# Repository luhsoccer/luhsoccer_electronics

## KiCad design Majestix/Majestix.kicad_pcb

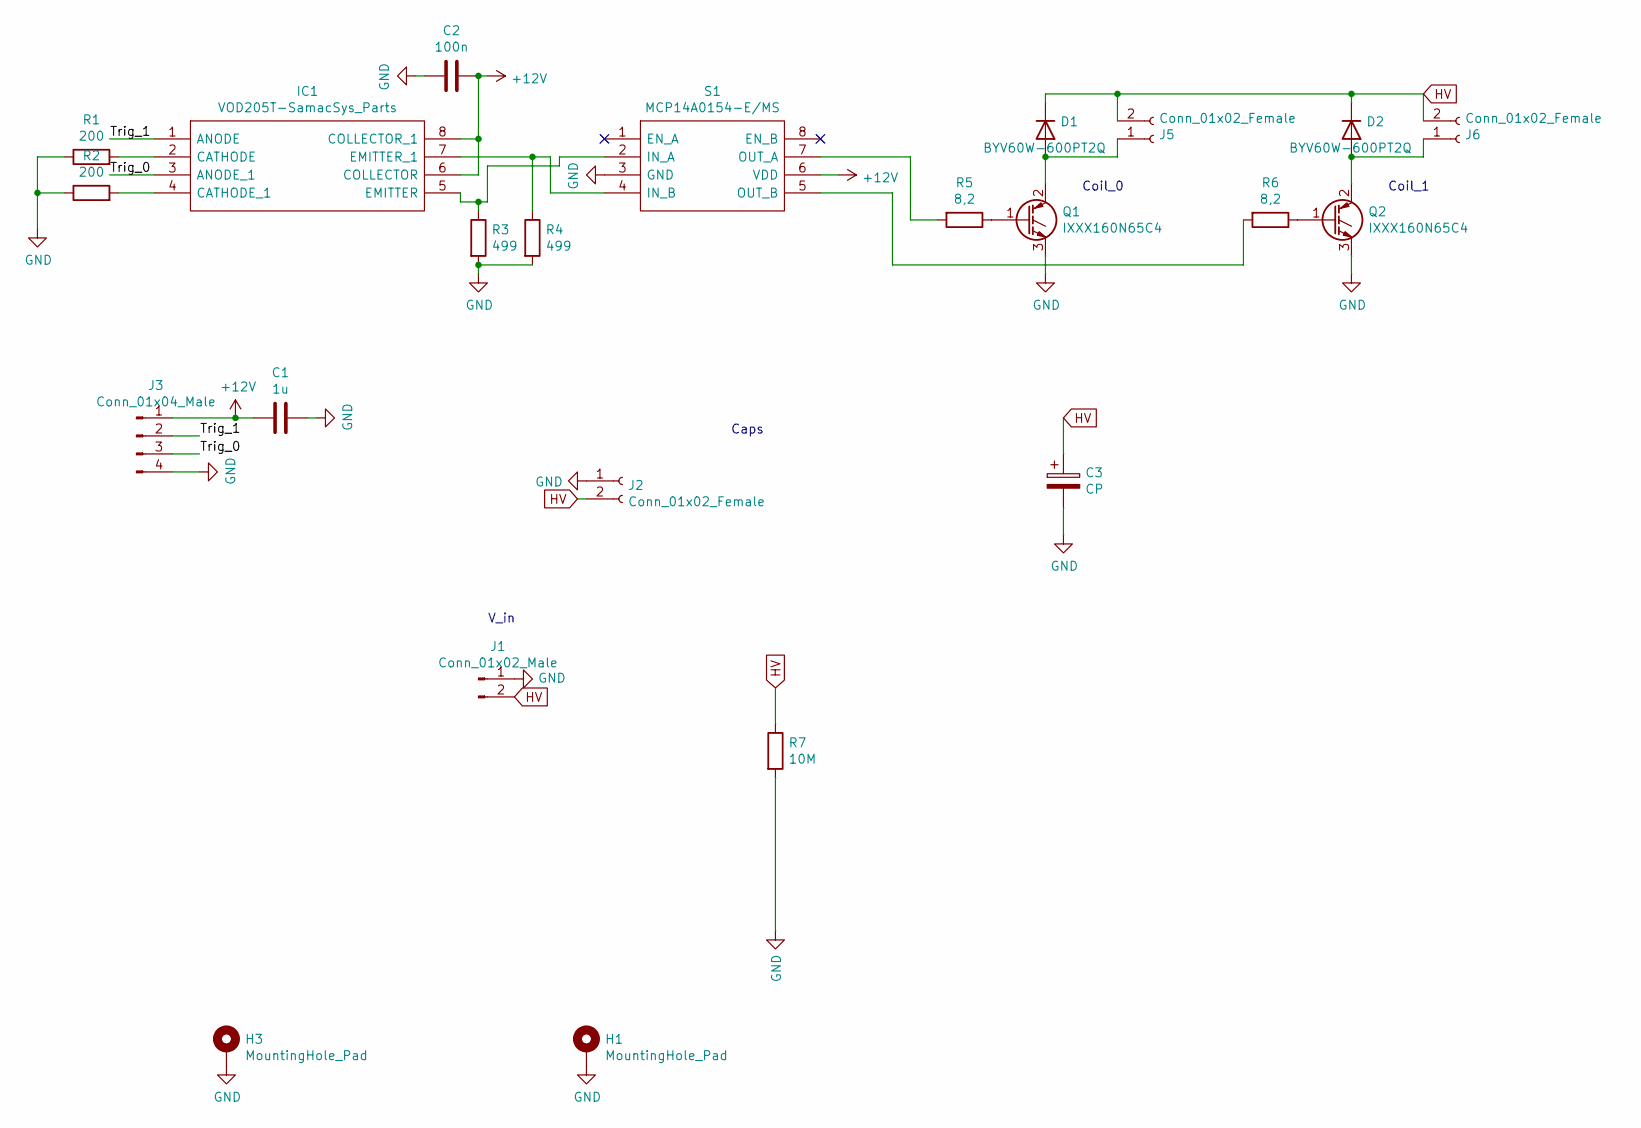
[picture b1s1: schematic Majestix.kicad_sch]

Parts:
C1: 1u; C_0805_2012Metric_Pad1.15x1.40mm_HandSolder
C2: 100n; C_0805_2012Metric_Pad1.15x1.40mm_HandSolder
C3: CP; CP_Radial_D30.0mm_P10.00mm_SnapIn
D1, D2: BYV60W-600PT2Q; TO-247-2_Vertical
H1, H3: MountingHole_Pad; MountingHole_3.2mm_M3_Pad_Via
IC1: VOD205T-SamacSys_Parts; SOIC-8_3.9x4.9mm_P1.27mm; Mouser Part Number 78-VOD205T
J1: Conn_01x02_Male; Molex_Micro-Fit_3.0_43650-0215_1x02_P3.00mm_Vertical
J2: Conn_01x02_Female; AMASS_XT30U-F_1x02_P5.0mm_Vertical_modified
J3: Conn_01x04_Male; JST_PH_B4B-PH-K_1x04_P2.00mm_Vertical
J5, J6: Conn_01x02_Female; AMASS_XT60-F_1x02_P7.20mm_Vertical_modified
Q1, Q2: IXXX160N65C4; TO-247-3_Vertical
R1, R2: 200; R_0805_2012Metric_Pad1.15x1.40mm_HandSolder
R3, R4: 499; R_0805_2012Metric_Pad1.15x1.40mm_HandSolder
R5, R6: 8,2; R_0805_2012Metric_Pad1.15x1.40mm_HandSolder
R7: 10M; R_2010_5025Metric_Pad1.52x2.65mm_HandSolder
S1: MCP14A0154-E/MS; MSOP-8_3x3mm_P0.65mm; Mouser Part Number 579-MCP14A0154-E/MS

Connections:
+12V: C1.2, C2.1, IC1.6 (COLLECTOR), IC1.8 (COLLECTOR_1), J3.1, S1.6 (VDD)
/Trig_0: IC1.3 (ANODE_1), J3.3
/Trig_1: IC1.1 (ANODE), J3.2
GND: C1.1, C2.2, C3.2, H1.1, H3.1, J1.1, J2.1, J3.4, Q1.3 (E), Q2.3 (E), R1.1, R2.1, R3.2, R4.2, R7.2, S1.3 (GND)
HV: C3.1, D1.1 (K), D2.1 (K), J1.2, J2.2, J5.2, J6.2, R7.1
unnamed: D1.2 (A), J5.1, Q1.2 (C)
unnamed: D2.2 (A), J6.1, Q2.2 (C)
unnamed: IC1.2 (CATHODE), R1.2
unnamed: IC1.4 (CATHODE_1), R2.2
unnamed: IC1.5 (EMITTER), R3.1, S1.2 (IN_A)
unnamed: IC1.7 (EMITTER_1), R4.1, S1.4 (IN_B)
unnamed: Q1.1 (G), R5.1
unnamed: Q2.1 (G), R6.1
unnamed: R5.2, S1.7 (OUT_A)
unnamed: R6.2, S1.5 (OUT_B)

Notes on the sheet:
Coil_0
V_in
Coil_1
Caps

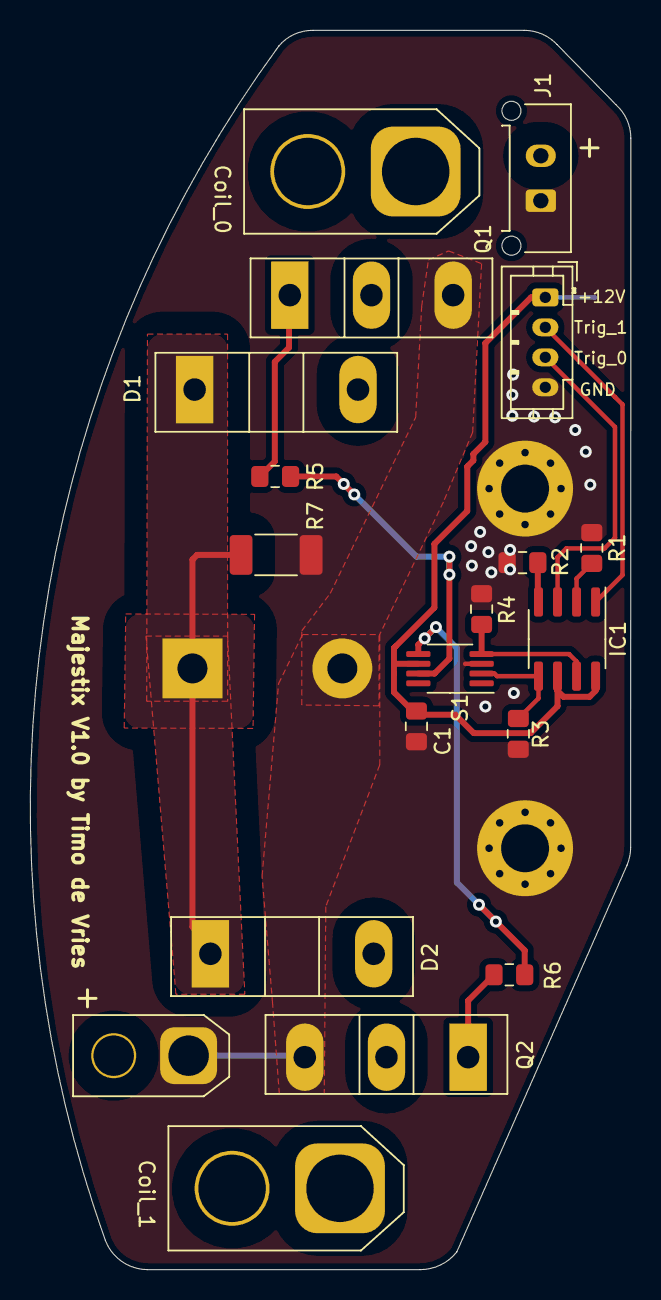
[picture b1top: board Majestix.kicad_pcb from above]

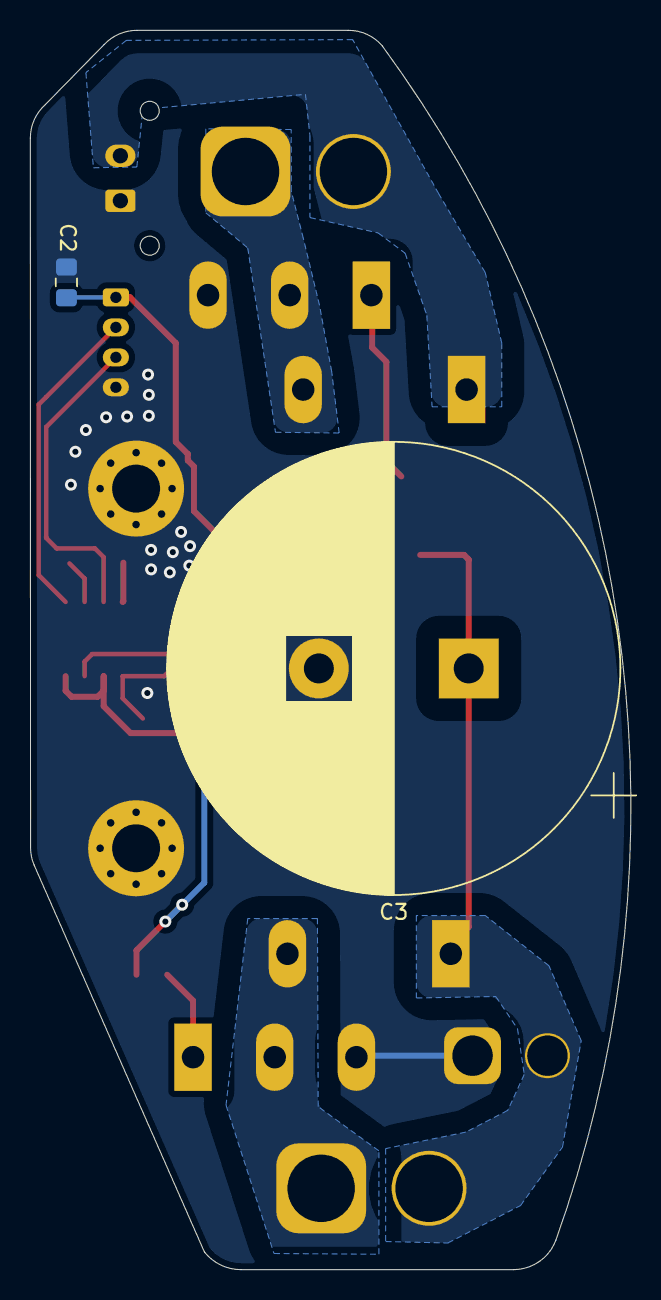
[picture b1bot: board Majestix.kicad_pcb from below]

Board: 2 copper layers, 40.1 x 82.7 mm, 23 parts (2 on the bottom side), 15 nets.

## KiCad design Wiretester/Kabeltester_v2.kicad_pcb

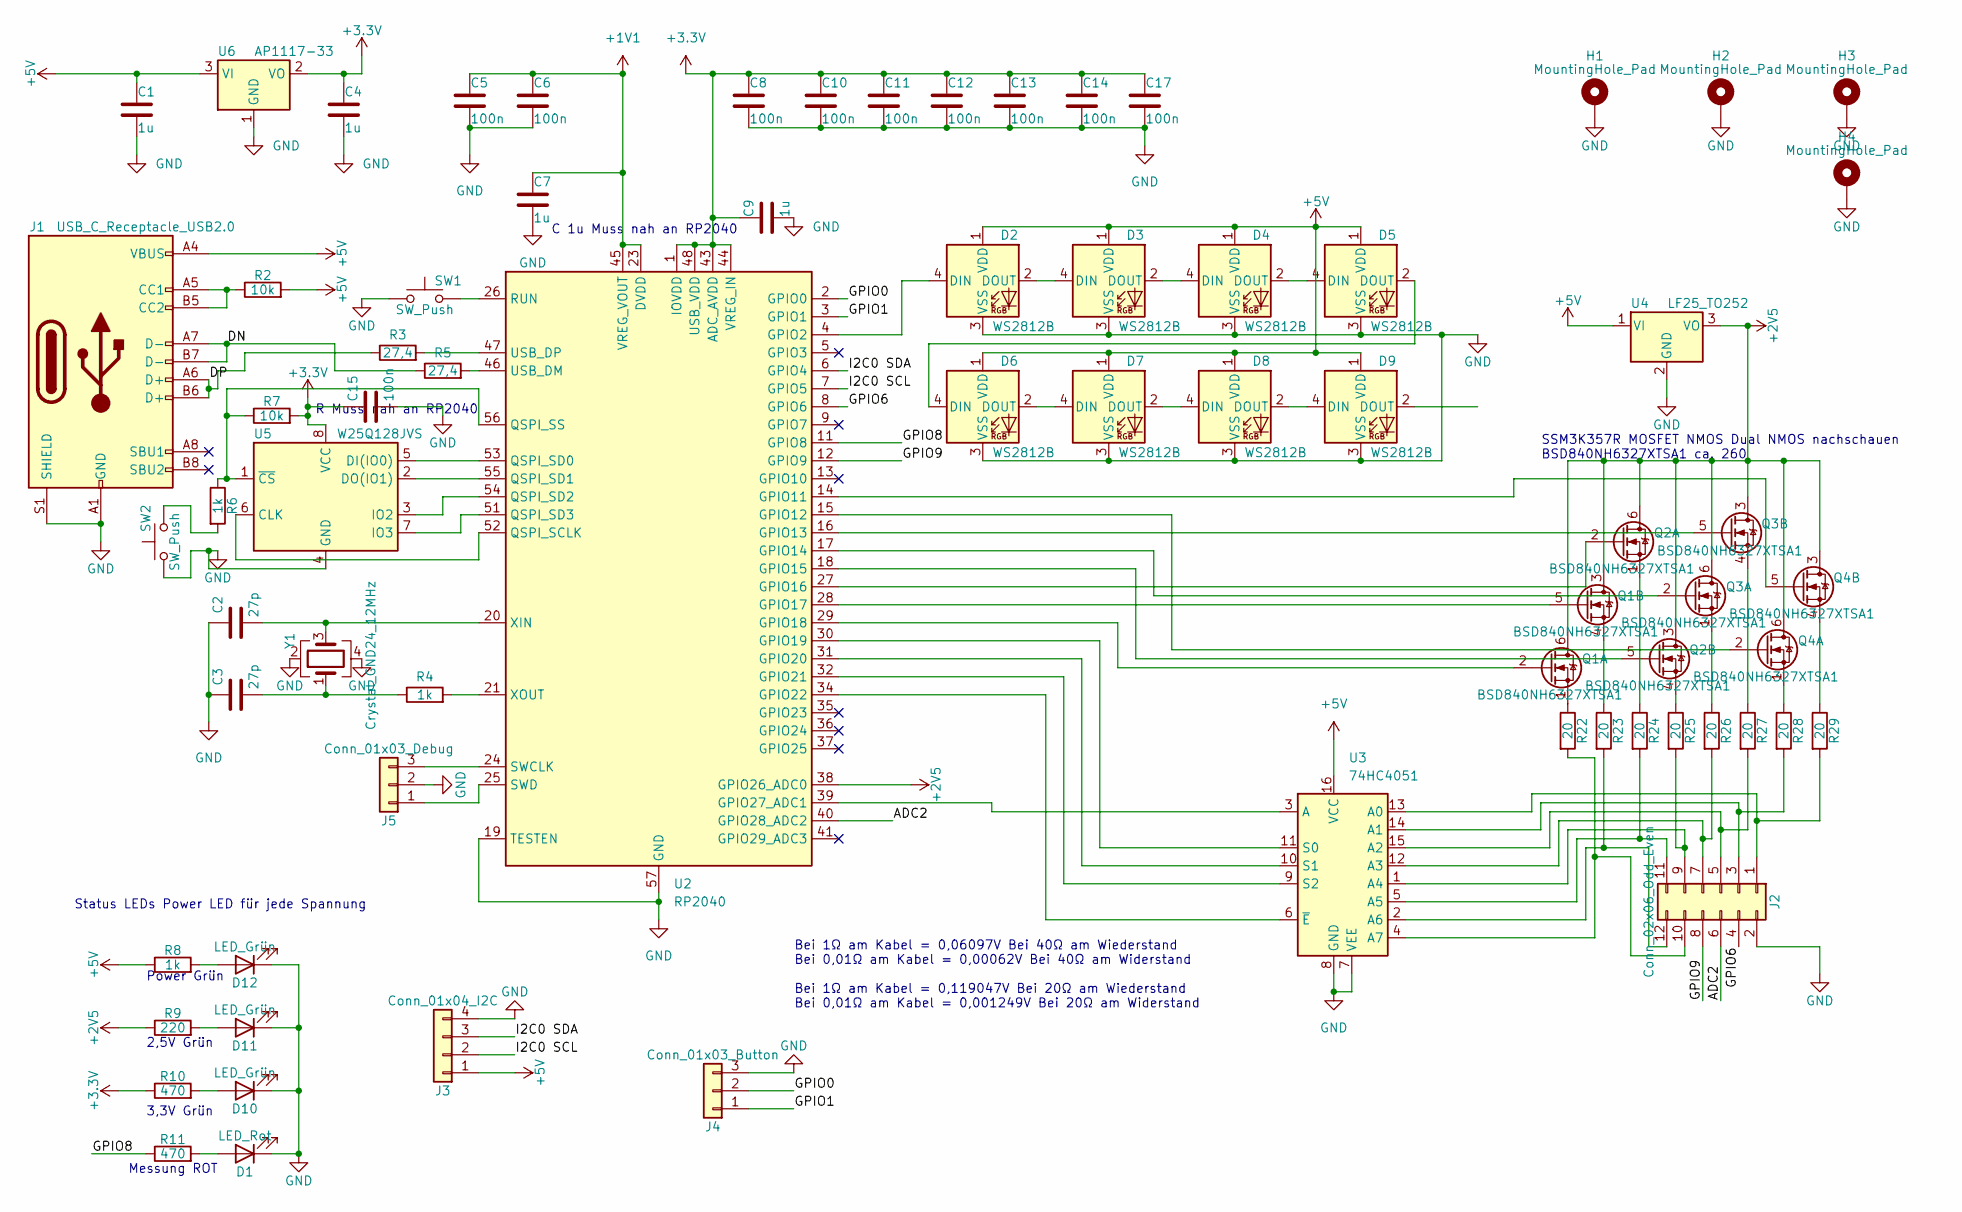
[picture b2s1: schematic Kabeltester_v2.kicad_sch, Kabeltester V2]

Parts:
C1, C4, C7, C9: 1u; C_0402_1005Metric_Pad0.74x0.62mm_HandSolder
C2, C3: 27p; C_0402_1005Metric_Pad0.74x0.62mm_HandSolder
C5, C6, C8, C10, C11, C12, C13, C14, C15, C17: 100n; C_0402_1005Metric_Pad0.74x0.62mm_HandSolder
D1: LED_Rot; LED_0603_1608Metric_Pad1.05x0.95mm_HandSolder
D2, D3, D4, D5, D6, D7, D8, D9: WS2812B; LED_WS2812B_PLCC4_5.0x5.0mm_P3.2mm
D10, D11, D12: LED_Grün; LED_0603_1608Metric_Pad1.05x0.95mm_HandSolder
H1, H2, H3, H4: MountingHole_Pad; MountingHole_3.2mm_M3_DIN965_Pad
J1: USB_C_Receptacle_USB2.0; USB_C_Receptacle_HRO_TYPE-C-31-M-12
J2: Conn_02x06_Odd_Even; PinSocket_2x06_P2.54mm_Vertical
J3: Conn_01x04_I2C; PinHeader_1x04_P2.54mm_Vertical
J4: Conn_01x03_Button; PinHeader_1x03_P2.54mm_Vertical
J5: Conn_01x03_Debug; PinHeader_1x03_P2.54mm_Vertical
Q1, Q2, Q3, Q4: BSD840NH6327XTSA1; SOT-363_SC-70-6_Handsoldering
R2, R7: 10k; R_0402_1005Metric_Pad0.72x0.64mm_HandSolder
R3, R5: 27,4; R_0402_1005Metric_Pad0.72x0.64mm_HandSolder
R4, R6, R8: 1k; R_0402_1005Metric_Pad0.72x0.64mm_HandSolder
R9: 220; R_0402_1005Metric_Pad0.72x0.64mm_HandSolder
R10, R11: 470; R_0402_1005Metric_Pad0.72x0.64mm_HandSolder
R22, R23, R24, R25, R26, R27, R28, R29: 20; R_2512_6332Metric_Pad1.40x3.35mm_HandSolder
SW1, SW2: SW_Push; SW_PUSH_6mm
U2: RP2040; QFN-56-1EP_7x7mm_P0.4mm_EP3.2x3.2mm
U3: 74HC4051; TSSOP-16_4.4x5mm_P0.65mm
U4: LF25_TO252; TO-252-2
U5: W25Q128JVS; SOIC-8_5.23x5.23mm_P1.27mm
U6: AP1117-33; SOT-23
Y1: Crystal_GND24_12MHz; Crystal_SMD_3225-4Pin_3.2x2.5mm_HandSoldering

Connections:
+1V1: C5.1, C6.1, C7.1, U2.23 (DVDD), U2.45 (VREG_VOUT), U2.50 (DVDD)
+2V5: Q1.3 (D), Q1.6 (D), Q2.3 (D), Q2.6 (D), Q3.3 (D), Q3.6 (D), Q4.3 (D), Q4.6 (D), R9.1, U2.38 (GPIO26_ADC0), U4.3 (VO)
+3.3V: C4.1, C8.1, C9.1, C10.1, C11.1, C12.1, C13.1, C14.1, C15.1, C17.1, R7.2, R10.1, U2.1 (IOVDD), U2.10 (IOVDD), U2.22 (IOVDD), U2.33 (IOVDD), U2.42 (IOVDD), U2.43 (ADC_AVDD), U2.44 (VREG_IN), U2.48 (USB_VDD), U2.49 (IOVDD), U5.8 (VCC), U6.2 (VO)
+5V: C1.1, D2.1 (VDD), D3.1 (VDD), D4.1 (VDD), D5.1 (VDD), D6.1 (VDD), D7.1 (VDD), D8.1 (VDD), D9.1 (VDD), J1.A4 (VBUS), J1.A9 (VBUS), J1.B4 (VBUS), J1.B9 (VBUS), J3.1, R2.2, R8.1, U3.16 (VCC), U4.1 (VI), U6.3 (VI)
/ADC2: J2.6, U2.40 (GPIO28_ADC2)
/DN: J1.A7 (D-), J1.B7 (D-), R5.1
/DP: J1.A6 (D+), J1.B6 (D+), R3.1
/GPIO0: J4.2, U2.2 (GPIO0)
/GPIO1: J4.1, U2.3 (GPIO1)
/GPIO6: J2.4, U2.8 (GPIO6)
/GPIO8: R11.1, U2.11 (GPIO8)
/GPIO9: J2.8, U2.12 (GPIO9)
/I2C0 SCL: J3.2, U2.7 (GPIO5)
/I2C0 SDA: J3.3, U2.6 (GPIO4)
GND: C1.2, C2.1, C3.1, C4.2, C5.2, C6.2, C7.2, C8.2, C9.2, C10.2, C11.2, C12.2, C13.2, C14.2, C15.2, C17.2, D1.1 (K), D2.3 (VSS), D3.3 (VSS), D4.3 (VSS), D5.3 (VSS), D6.3 (VSS), D7.3 (VSS), D8.3 (VSS), D9.3 (VSS), D10.1 (K), D11.1 (K), D12.1 (K), H1.1, H2.1, H3.1, H4.1, J1.A1 (GND), J1.A12 (GND), J1.B1 (GND), J1.B12 (GND), J1.S1 (SHIELD), J2.2, J3.4, J4.3, J5.2, SW1.1, SW2.1, U2.19 (TESTEN), U2.57 (GND), U3.7 (VEE), U3.8 (GND), U4.2 (GND), U5.4 (GND), U6.1 (GND), Y1.2, Y1.4
unnamed: C3.2, R4.1, Y1.1
unnamed: D1.2 (A), R11.2
unnamed: D2.4 (DIN), U2.4 (GPIO2)
unnamed: D2.2 (DOUT), D3.4 (DIN)
unnamed: D3.2 (DOUT), D4.4 (DIN)
unnamed: D4.2 (DOUT), D5.4 (DIN)
unnamed: D5.2 (DOUT), D6.4 (DIN)
unnamed: D6.2 (DOUT), D7.4 (DIN)
unnamed: D7.2 (DOUT), D8.4 (DIN)
unnamed: D8.2 (DOUT), D9.4 (DIN)
unnamed: D10.2 (A), R10.2
unnamed: D11.2 (A), R9.2
unnamed: D12.2 (A), R8.2
unnamed: J1.A5 (CC1), J1.B5 (CC2), R2.1
unnamed: J2.1, R29.2, U3.13 (A0)
unnamed: J2.3, R28.2, U3.14 (A1)
unnamed: J2.5, R27.2, U3.15 (A2)
unnamed: J2.7, R26.2, U3.12 (A3)
unnamed: J2.9, R25.2, U3.1 (A4)
unnamed: J2.10, R22.2, U3.4 (A7)
unnamed: J2.11, R24.2, U3.5 (A5)
unnamed: J2.12, R23.2, U3.2 (A6)
unnamed: J5.1, U2.25 (SWD)
unnamed: J5.3, U2.24 (SWCLK)
unnamed: Q1.2 (G), U2.29 (GPIO18)
unnamed: Q1.1 (S), R22.1
unnamed: Q1.5 (G), U2.28 (GPIO17)
unnamed: Q1.4 (S), R23.1
unnamed: Q2.2 (G), U2.27 (GPIO16)
unnamed: Q2.1 (S), R24.1
unnamed: Q2.5 (G), U2.18 (GPIO15)
unnamed: Q2.4 (S), R25.1
unnamed: Q3.2 (G), U2.17 (GPIO14)
unnamed: Q3.1 (S), R26.1
unnamed: Q3.5 (G), U2.16 (GPIO13)
unnamed: Q3.4 (S), R27.1
unnamed: Q4.2 (G), U2.15 (GPIO12)
unnamed: Q4.1 (S), R28.1
unnamed: Q4.5 (G), U2.14 (GPIO11)
unnamed: Q4.4 (S), R29.1
unnamed: R6.2, SW2.2
unnamed: U2.30 (GPIO19), U3.11 (S0)
unnamed: U2.31 (GPIO20), U3.10 (S1)
unnamed: U2.32 (GPIO21), U3.9 (S2)
unnamed: U2.34 (GPIO22), U3.6 (~E)
unnamed: U2.39 (GPIO27_ADC1), U3.3 (A)
unnamed: U2.52 (QSPI_SCLK), U5.6 (CLK)
unnamed: U2.53 (QSPI_SD0), U5.5 (DI(IO0))
unnamed: U2.55 (QSPI_SD1), U5.2 (DO(IO1))
unnamed: U2.54 (QSPI_SD2), U5.3 (IO2)
unnamed: U2.51 (QSPI_SD3), U5.7 (IO3)
unnamed: R6.1, R7.1, U2.56 (QSPI_SS), U5.1 (~CS)
unnamed: SW1.2, U2.26 (RUN)
unnamed: R5.2, U2.46 (USB_DM)
unnamed: R3.2, U2.47 (USB_DP)
unnamed: C2.2, U2.20 (XIN), Y1.3
unnamed: R4.2, U2.21 (XOUT)

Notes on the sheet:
3,3V Grün
Status LEDs Power LED für jede Spannung
SSM3K357R MOSFET NMOS Dual NMOS nachschauen BSD840NH6327XTSA1 ca. 260
Bei 1Ω am Kabel = 0,06097V Bei 40Ω am Wiederstand Bei 0,01Ω am Kabel = 0,00062V Bei 40Ω am Widerstand Bei 1Ω am Kabel = 0,119047V Bei 20Ω am Wiederstand Bei 0,01Ω am Kabel = 0,001249V Bei 20Ω am Widerstand
Power Grün
Messung ROT
2,5V Grün
R Muss nah an RP2040
C 1u Muss nah an RP2040

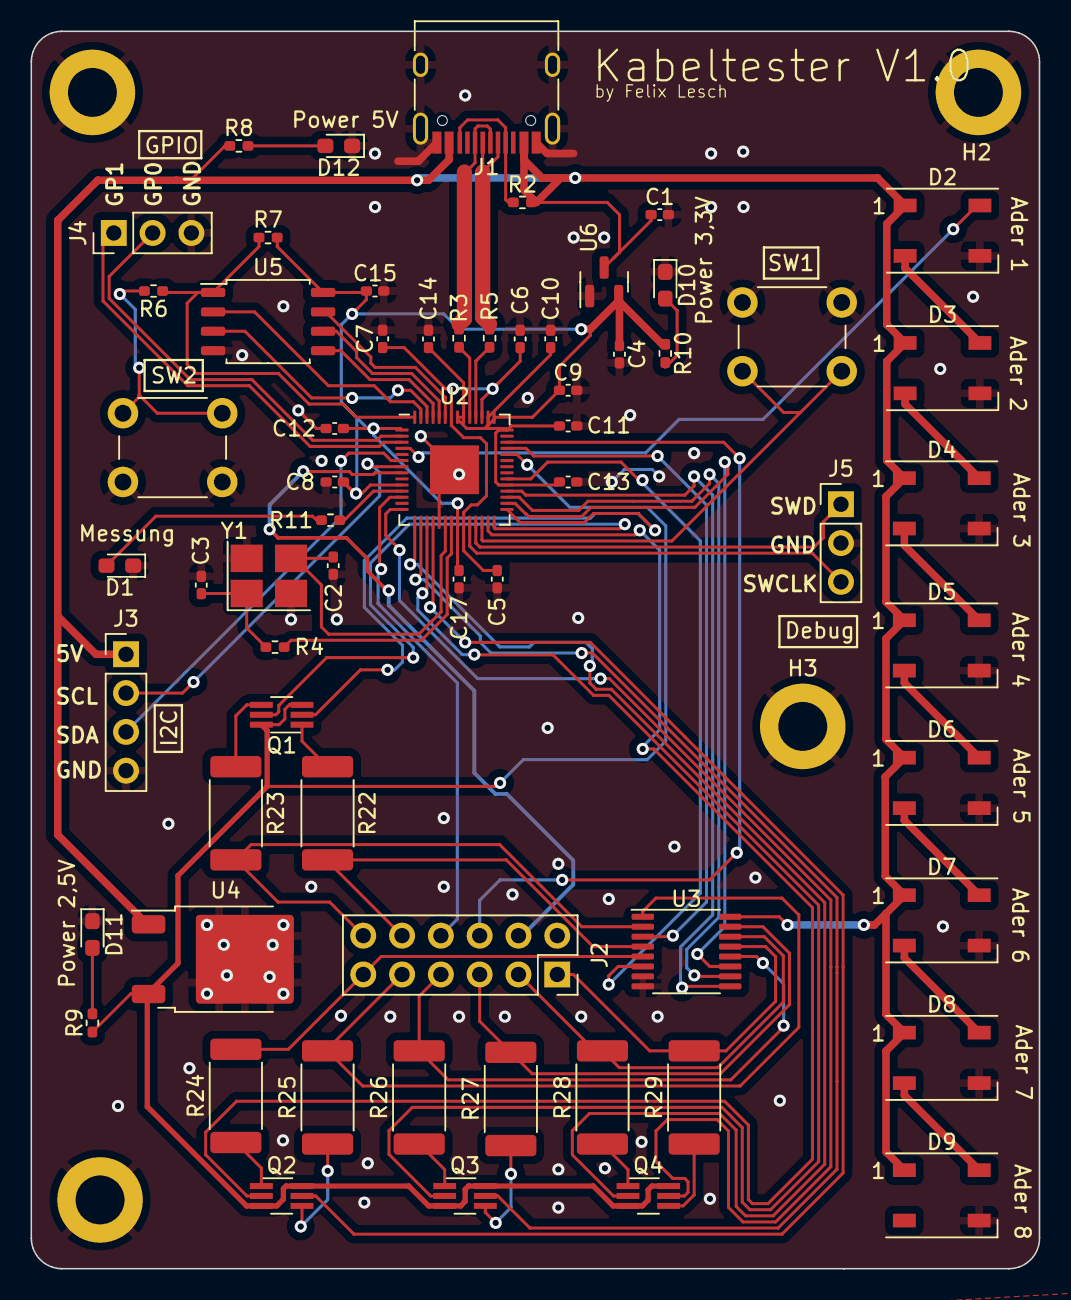
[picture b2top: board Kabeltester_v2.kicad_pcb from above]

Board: 2 copper layers, 66.0 x 81.0 mm, 67 parts (0 on the bottom side), 72 nets.
